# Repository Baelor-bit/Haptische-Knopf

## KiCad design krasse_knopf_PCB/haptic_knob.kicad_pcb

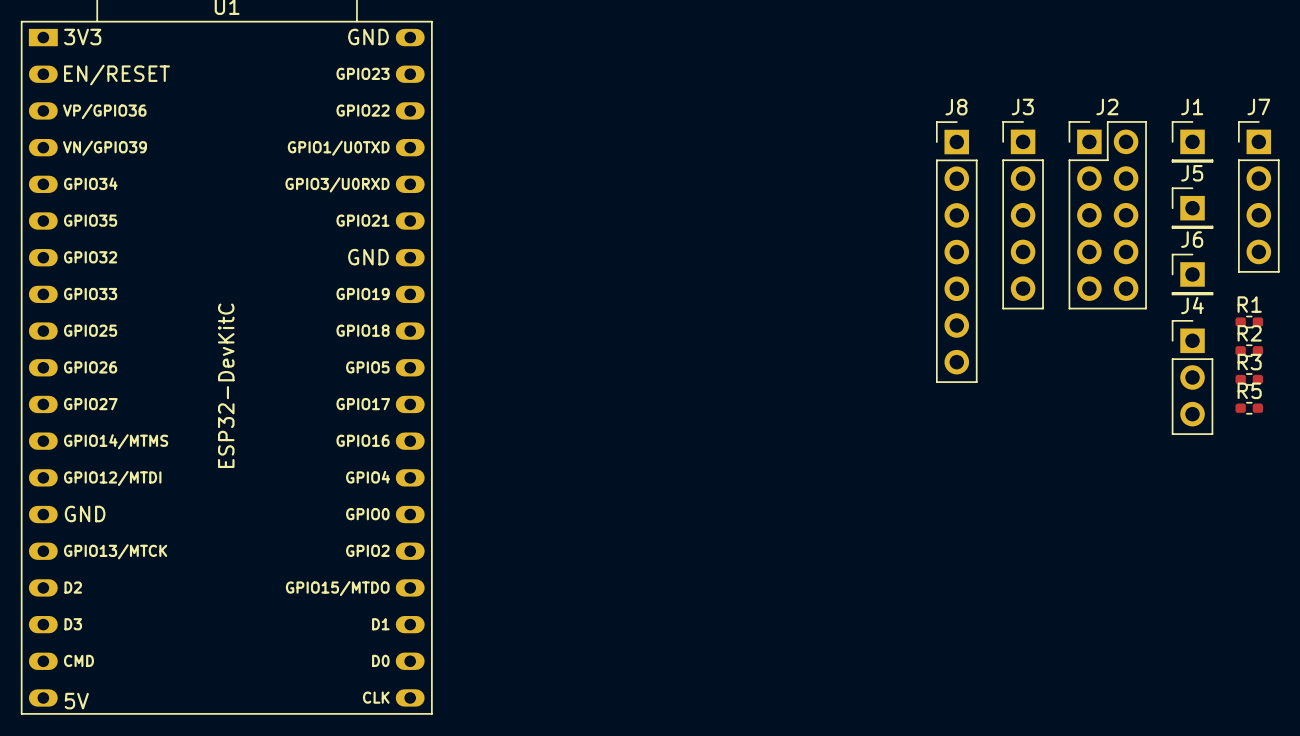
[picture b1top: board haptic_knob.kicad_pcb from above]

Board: 2 copper layers, 13 parts (0 on the bottom side), 20 nets, no tracks yet.

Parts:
J1: SimpleFOC_Plus; PinHeader_1x01_P2.54mm_Vertical
J2: SimpleFOC_ctrl; PinHeader_2x05_P2.54mm_Vertical
J3: HX711_Sensor; PinHeader_1x05_P2.54mm_Vertical
J4: SimpleFOC_motor; PinHeader_1x03_P2.54mm_Vertical
J5: SimpleFOC_Minus; PinHeader_1x01_P2.54mm_Vertical
J6: 5V; PinHeader_1x01_P2.54mm_Vertical
J7: HX711_Data; PinHeader_1x04_P2.54mm_Vertical
J8: Display; PinHeader_1x07_P2.54mm_Vertical
R1, R3: R_Variable; R_0402_1005Metric_Pad0.72x0.64mm_HandSolder
R2, R5: 1k; R_0402_1005Metric_Pad0.72x0.64mm_HandSolder
U1: ESP32-DevKitC

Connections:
+3V3: J2.10, J7.1, J8.7, U1.1 (3V3)
/BLK: J3.2, R3.2, R5.2
/CLK: J7.3, U1.28 (GPIO17)
/CS: J8.2, U1.29 (GPIO5)
/DC: J8.3, U1.31 (GPIO19)
/EN: J2.2, U1.7 (32K_XP/GPIO32/ADC1_CH4)
/GRN: J3.4, R2.2, R3.1
/IN1: J2.5, U1.9 (DAC_1/ADC2_CH8/GPIO25)
/IN2: J2.4, U1.10 (DAC_2/ADC2_CH9/GPIO26)
/IN3: J2.3, U1.11 (ADC2_CH7/GPIO27)
/RED: J3.1, R1.1, R2.1
/RST: J8.1, U1.12 (MTMS/GPIO14/ADC2_CH6)
/SCL: J8.5, U1.30 (GPIO18)
/SDA: J8.4, U1.37 (GPIO23)
/WHT: J3.3, R1.2, R5.1
/nFT: J2.6, U1.5 (VDET_1/GPIO34/ADC1_CH6)
/nRT: J2.8, U1.26 (ADC2_CH0/GPIO4)
/nSP: J2.7, U1.8 (32K_XN/GPIO33/ADC1_CH5)
GND: J2.1, J2.9, J7.4, J8.6, U1.14 (GND), U1.32 (GND), U1.38 (GND)
unnamed: J6.1 (Pin_1_1), U1.19 (5V)
